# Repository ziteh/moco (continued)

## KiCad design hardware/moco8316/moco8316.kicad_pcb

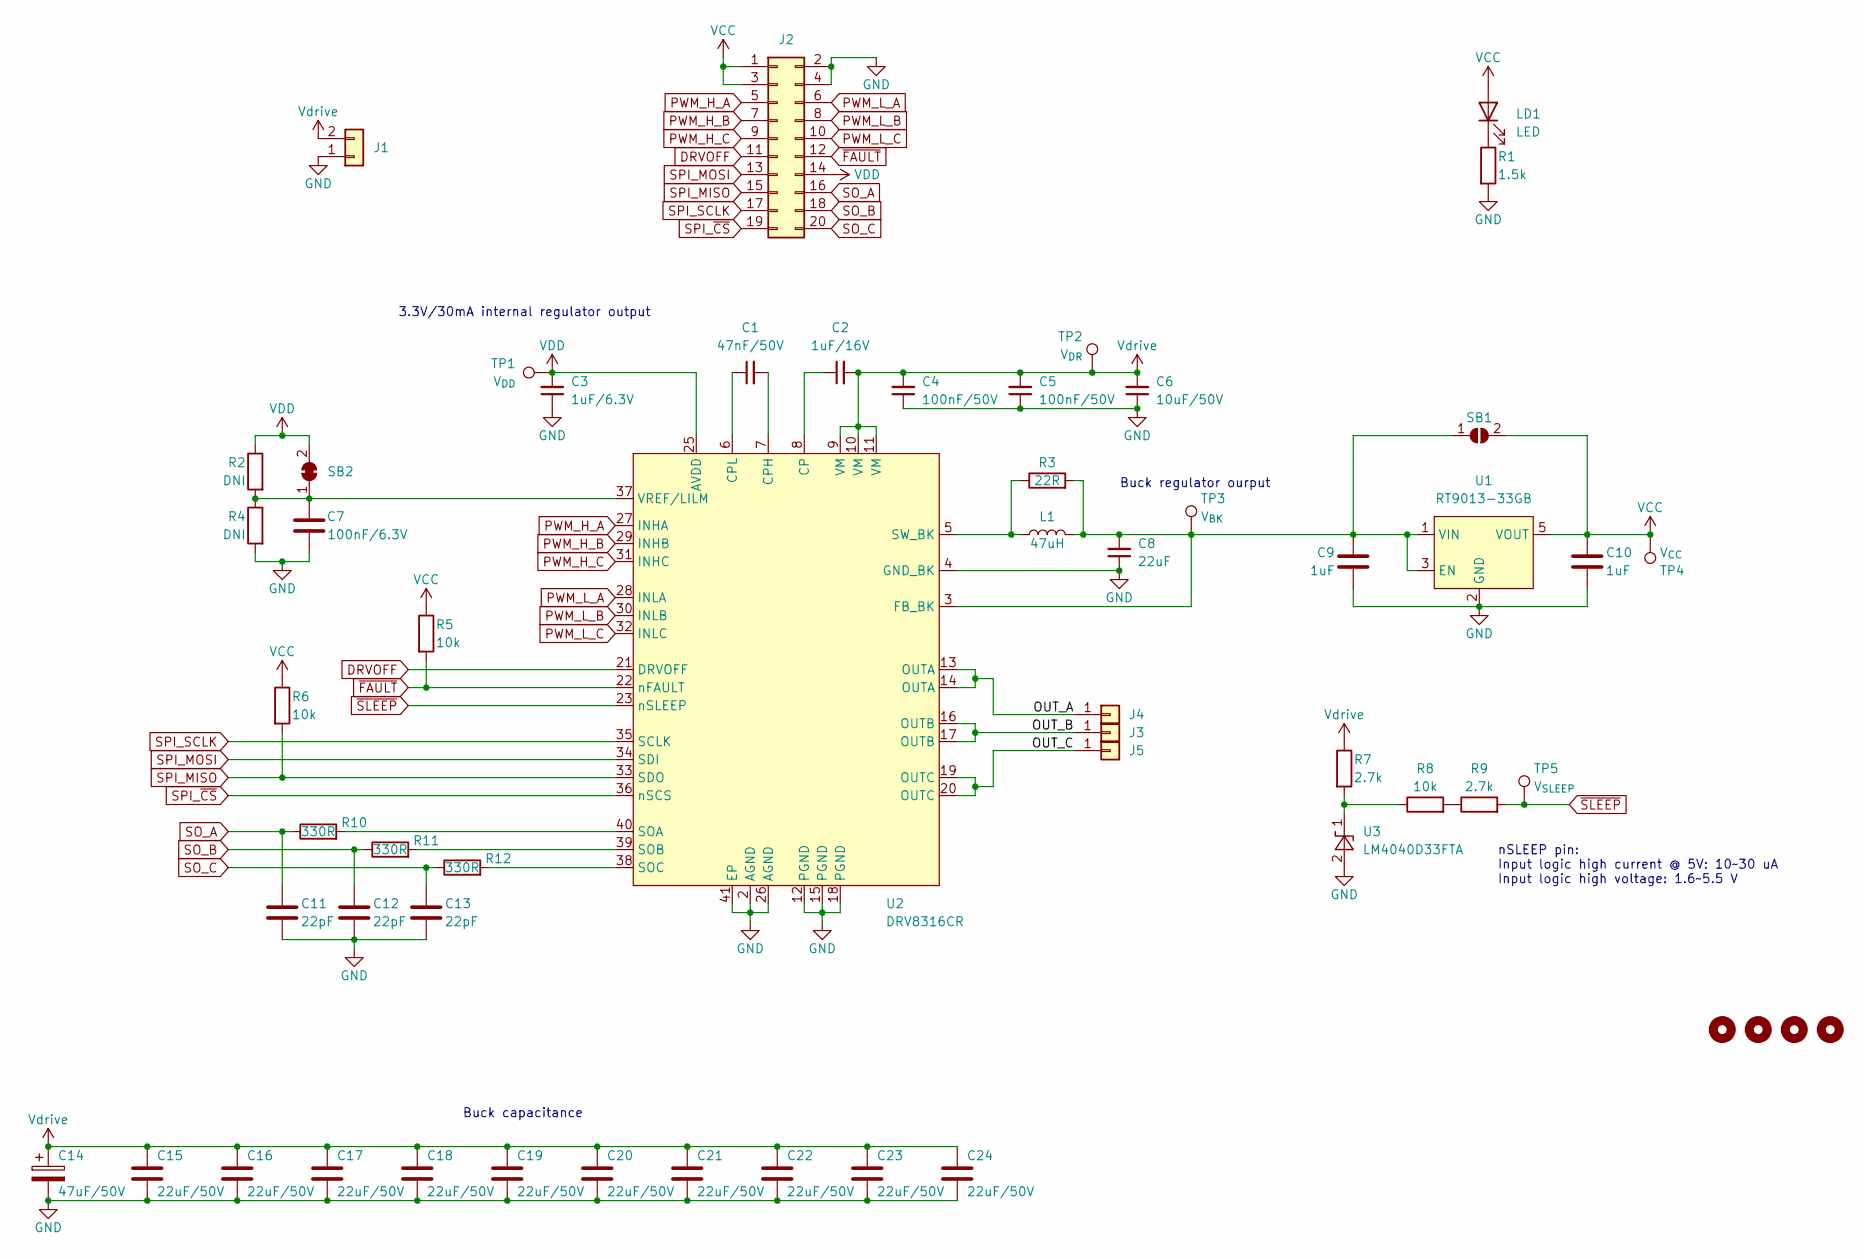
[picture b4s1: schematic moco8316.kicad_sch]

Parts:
C1: 47nF/50V; C_0603_1608Metric
C2: 1uF/16V; C_0603_1608Metric
C3: 1uF/6.3V; C_0603_1608Metric
C4, C5: 100nF/50V; C_0603_1608Metric
C6: 10uF/50V; C_0805_2012Metric; MFR. Part# GRM21BR61H106KE43L; LCSC C440198
C7: 100nF/6.3V; C_0603_1608Metric
C8: 22uF; C_0603_1608Metric
C9, C10: 1uF; C_0603_1608Metric
C11, C12, C13: 22pF; C_0603_1608Metric
C14: 47uF/50V; CP_Elec_6.3x7.7; MFR. Part# 50CE47AX; LCSC C179814
C15, C16, C17, C18, C19, C20, C21, C22, C23, C24: 22uF/50V; C_0805_2012Metric
H1, H2, H3, H4: MountingHole; MountingHole_3.2mm_M3
J1: Conn_01x02; AMASS_XT30UPB-M_1x02_P5.0mm_Vertical
J2: Conn_02x10_Odd_Even; PinSocket_2x10_P2.54mm_Vertical
J3, J4, J5: Conn_01x01; wire_3.2mm
L1: 47uH; L_Taiyo-Yuden_NR-50xx; MFR. Part# SM4532-470MT; LCSC C9899
LD1: LED; LED_0805_2012Metric_Pad1.15x1.40mm_HandSolder
R1: 1.5k; R_0603_1608Metric
R2, R4: DNI; R_0603_1608Metric
R3: 22R; R_0603_1608Metric
R5, R6, R8: 10k; R_0603_1608Metric
R7, R9: 2.7k; R_0603_1608Metric
R10, R11, R12: 330R; R_0603_1608Metric
SB1: SolderJumper_2_Open; SolderJumper-2_P1.3mm_Open_RoundedPad1.0x1.5mm
SB2: SolderJumper_2_Bridged; SolderJumper-2_P1.3mm_Bridged_RoundedPad1.0x1.5mm
TP1: V_{DD}; TestPoint_Pad_D1.0mm
TP2: V_{DR}; TestPoint_Pad_D1.0mm
TP3: V_{BK}; TestPoint_Pad_D1.0mm
TP4: V_{CC}; TestPoint_Pad_D1.0mm
TP5: V_{SLEEP}; TestPoint_Pad_D1.0mm
U1: RT9013-33GB; SOT-23-5
U2: DRV8316CR; VQFN-40_RGF_5x7mm_0.5mm_pitch_thermalpad
U3: LM4040D33FTA; SOT-23

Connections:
/OUT_A: J4.1, U2.13 (OUTA), U2.14 (OUTA)
/OUT_B: J3.1, U2.16 (OUTB), U2.17 (OUTB)
/OUT_C: J5.1, U2.19 (OUTC), U2.20 (OUTC)
DRVOFF: J2.11, U2.21 (DRVOFF)
GND: C3.1, C4.1, C5.1, C6.1, C7.2, C8.1, C9.2, C10.2, C11.2, C12.2, C13.2, C14.2, C15.2, C16.2, C17.2, C18.2, C19.2, C20.2, C21.2, C22.2, C23.2, C24.2, J1.1, J2.2, J2.4, R1.2, R4.2, U1.2 (GND), U2.2 (AGND), U2.4 (GND_BK), U2.12 (PGND), U2.15 (PGND), U2.18 (PGND), U2.26 (AGND), U2.41 (EP), U3.2 (A)
unnamed: LD1.1 (K), R1.1
unnamed: R8.2, R9.1
unnamed: C8.2, C9.1, L1.2, R3.2, SB1.1 (A), TP3.1, U1.1 (VIN), U1.3 (EN), U2.3 (FB_BK)
unnamed: C7.1, R2.2, R4.1, SB2.1 (A), U2.37 (VREF/LILM)
unnamed: C2.1, U2.8 (CP)
unnamed: C1.2, U2.7 (CPH)
unnamed: C1.1, U2.6 (CPL)
unnamed: R10.2, U2.40 (SOA)
unnamed: R11.2, U2.39 (SOB)
unnamed: R12.2, U2.38 (SOC)
unnamed: L1.1, R3.1, U2.5 (SW_BK)
unnamed: R7.2, R8.1, U3.1 (K)
PWM_H_A: J2.5, U2.27 (INHA)
PWM_H_B: J2.7, U2.29 (INHB)
PWM_H_C: J2.9, U2.31 (INHC)
PWM_L_A: J2.6, U2.28 (INLA)
PWM_L_B: J2.8, U2.30 (INLB)
PWM_L_C: J2.10, U2.32 (INLC)
SO_A: C11.1, J2.16, R10.1
SO_B: C12.1, J2.18, R11.1
SO_C: C13.1, J2.20, R12.1
SPI_MISO: J2.15, R6.2, U2.33 (SDO)
SPI_MOSI: J2.13, U2.34 (SDI)
SPI_SCLK: J2.17, U2.35 (SCLK)
SPI_~CS: J2.19, U2.36 (nSCS)
VCC: C10.1, J2.1, J2.3, LD1.2 (A), R5.1, R6.1, SB1.2 (B), TP4.1, U1.5 (VOUT)
VDD: C3.2, J2.14, R2.1, SB2.2 (B), TP1.1, U2.25 (AVDD)
Vdrive: C2.2, C4.2, C5.2, C6.2, C14.1, C15.1, C16.1, C17.1, C18.1, C19.1, C20.1, C21.1, C22.1, C23.1, C24.1, J1.2, R7.1, TP2.1, U2.9 (VM), U2.10 (VM), U2.11 (VM)
~FAULT: J2.12, R5.2, U2.22 (nFAULT)
~SLEEP: R9.2, TP5.1, U2.23 (nSLEEP)

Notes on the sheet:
3.3V/30mA internal regulator output
nSLEEP pin: Input logic high current @ 5V: 10~30 uA Input logic high voltage: 1.6~5.5 V
Buck regulator ourput
Buck capacitance

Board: 2 copper layers, 57 parts (0 on the bottom side), 35 nets, no tracks yet.

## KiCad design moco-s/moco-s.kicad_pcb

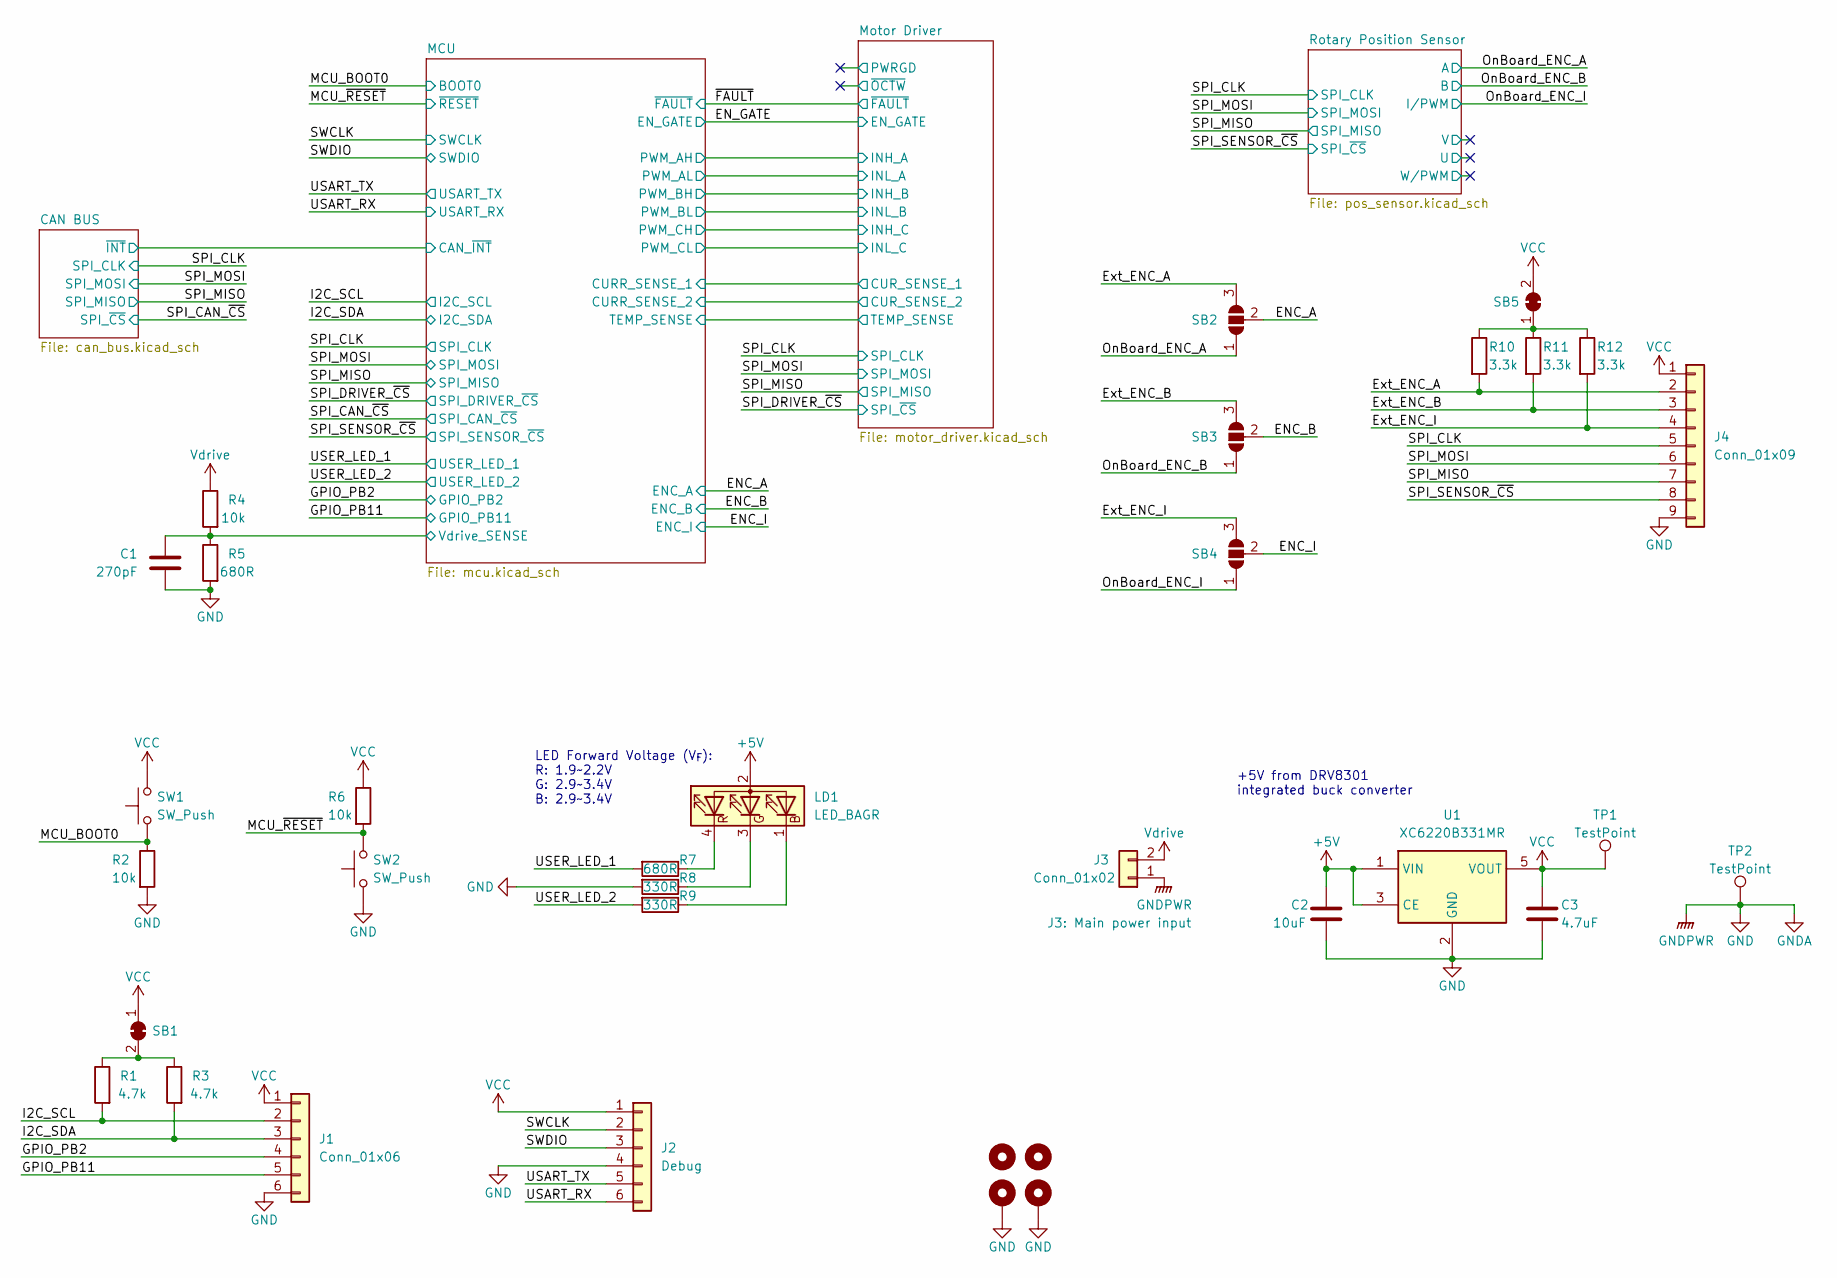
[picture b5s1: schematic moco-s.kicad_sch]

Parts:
C1: 270pF; C_0402_1005Metric; MFR.Part # GCM1555C1H271JA16D; JLCPCB Part # C524551
C2: 10uF; C_0402_1005Metric; MFR.Part # CL05A106MQ5NUNC; JLCPCB Part # C15525
C3: 4.7uF; C_0402_1005Metric; MFR.Part # CL05A475MP5NRNC; JLCPCB Part # C23733
H1, H3: MountingHole; MountingHole_2.2mm_M2_ISO14580
H2, H4: MountingHole_Pad; MountingHole_2.2mm_M2_Pad_Via
J1: Conn_01x06; JST_GH_SM06B-GHS-TB_1x06-1MP_P1.25mm_Horizontal; MFR.Part # GH1.25-6PWBPZ; JLCPCB Part # C2829255
J2: Debug; PinHeader_1x06_P2.54mm_Vertical
J3: Conn_01x02; AMASS_XT60-M_1x02_P7.20mm_Vertical; MFR.Part # XT60; JLCPCB Part # C98733
J4: Conn_01x09; JST_GH_SM09B-GHS-TB_1x09-1MP_P1.25mm_Horizontal; MFR.Part # GH1.25-9PWBPZ; JLCPCB Part # C2829258
LD1: LED_BAGR; RGB LED 1.6x1.6mm; MFR.Part # E6C0606RGBC3UDA; JLCPCB Part # C375569
R1, R3: 4.7k; R_0402_1005Metric; MFR.Part # 0402WGF4701TCE; JLCPCB Part # C25900
R2, R4, R6: 10k; R_0402_1005Metric; MFR.Part # 0402WGF1002TCE; JLCPCB Part # C25744
R5, R7: 680R; R_0402_1005Metric; MFR.Part # 0402WGF6800TCE; JLCPCB Part # C25130
R8, R9: 330R; R_0402_1005Metric; MFR.Part # 0402WGF3300TCE; JLCPCB Part # C25104
R10, R11, R12: 3.3k; R_0402_1005Metric; MFR.Part # 0402WGF3301TCE; JLCPCB Part # C25890
SB1, SB5: SolderJumper_2_Bridged; SolderJumper-2_P1.3mm_Bridged_RoundedPad1.0x1.5mm
SB2, SB3, SB4: Jumper_3_Bridged12; SolderJumper-3_P1.3mm_Open_RoundedPad1.0x1.5mm_NumberLabels
SW1, SW2: SW_Push; SW_SPST_CK_RS282G05A3; MFR.Part # TS-1092S-B3D2-G; JLCPCB Part # C520860
TP1, TP2: TestPoint; TestPoint_Pad_D2.0mm
U1: XC6220B331MR; SOT-23-5; MFR.Part # XC6220B331MR-G; JLCPCB Part # C86534

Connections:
+5V: C2.1, LD1.2 (A), U1.1 (VIN), U1.3 (CE); also elsewhere on the board
/ENC_A: SB2.2 (C); also elsewhere on the board
/ENC_B: SB3.2 (C); also elsewhere on the board
/ENC_I: SB4.2 (C); also elsewhere on the board
/Ext_ENC_A: J4.2, R10.2, SB2.3 (B)
/Ext_ENC_B: J4.3, R11.2, SB3.3 (B)
/Ext_ENC_I: J4.4, R12.2, SB4.3 (B)
/GPIO_PB2: J1.4; also elsewhere on the board
/GPIO_PB11: J1.5; also elsewhere on the board
/I2C_SCL: J1.2, R1.2; also elsewhere on the board
/I2C_SDA: J1.3, R3.2; also elsewhere on the board
/MCU/Vdrive_SENSE: C1.1, R4.2, R5.1; also elsewhere on the board
/MCU_BOOT0: R2.1, SW1.1; also elsewhere on the board
/MCU_~RESET: R6.2, SW2.2; also elsewhere on the board
/OnBoard_ENC_A: SB2.1 (A); also elsewhere on the board
/OnBoard_ENC_B: SB3.1 (A); also elsewhere on the board
/OnBoard_ENC_I: SB4.1 (A); also elsewhere on the board
/SPI_CLK: J4.5; also elsewhere on the board
/SPI_MISO: J4.7; also elsewhere on the board
/SPI_MOSI: J4.6; also elsewhere on the board
/SPI_SENSOR_~CS: J4.8; also elsewhere on the board
/SWCLK: J2.2; also elsewhere on the board
/SWDIO: J2.3; also elsewhere on the board
/USART_RX: J2.6; also elsewhere on the board
/USART_TX: J2.5; also elsewhere on the board
/USER_LED_1: R7.2; also elsewhere on the board
/USER_LED_2: R9.2; also elsewhere on the board
GND: C1.2, C2.2, C3.2, H2.1, H4.1, J1.6, J2.4, J3.1, J4.9, R2.2, R5.2, R8.2, SW2.1, TP2.1, U1.2 (GND); also elsewhere on the board
unnamed: LD1.1 (BK), R9.1
unnamed: LD1.3 (GK), R8.1
unnamed: LD1.4 (RK), R7.1
unnamed: R1.1, R3.1, SB1.2 (B)
unnamed: R10.1, R11.1, R12.1, SB5.1 (A)
VCC: C3.1, J1.1, J2.1, J4.1, R6.1, SB1.1 (A), SB5.2 (B), SW1.2, TP1.1, U1.5 (VOUT); also elsewhere on the board
Vdrive: J3.2, R4.1; also elsewhere on the board

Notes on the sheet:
LED Forward Voltage (V_{F}): R: 1.9~2.2V G: 2.9~3.4V B: 2.9~3.4V
+5V from DRV8301 integrated buck converter

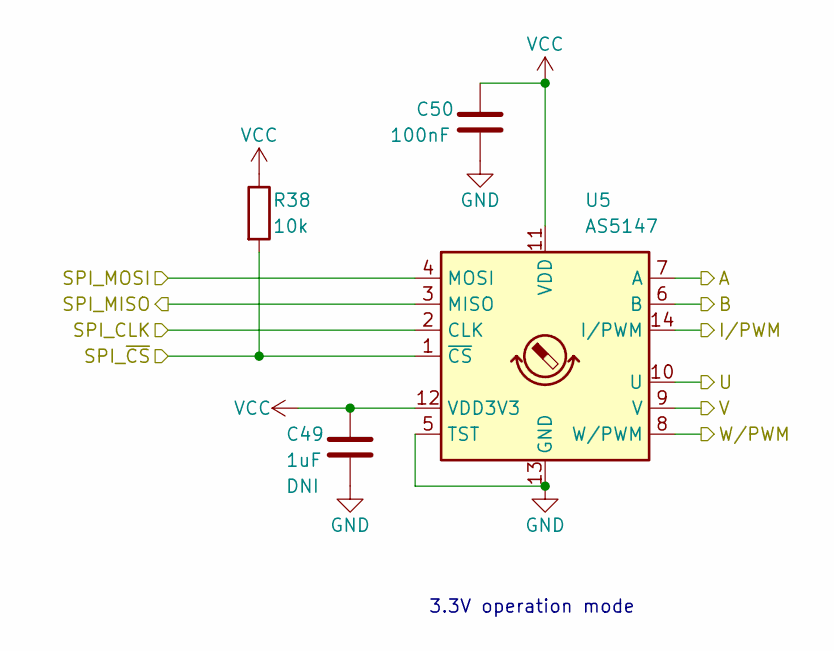
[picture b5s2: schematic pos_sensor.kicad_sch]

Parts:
C49: 1uF; C_0603_1608Metric
C50: 100nF; C_0603_1608Metric
R38: 10k; R_0402_1005Metric; MFR.Part # 0402WGF1002TCE; JLCPCB Part # C25744
U5: AS5147; TSSOP-14_4.4x5mm_P0.65mm; MFR.Part # AS5147P-HTSM; JLCPCB Part # C481876

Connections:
/OnBoard_ENC_A: U5.7 (A); also elsewhere on the board
/OnBoard_ENC_B: U5.6 (B); also elsewhere on the board
/OnBoard_ENC_I: U5.14 (I/PWM); also elsewhere on the board
/Rotary Position Sensor/U: U5.10 (U)
/Rotary Position Sensor/V: U5.9 (V)
/Rotary Position Sensor/W/PWM: U5.8 (W/PWM)
/SPI_CLK: U5.2 (CLK); also elsewhere on the board
/SPI_MISO: U5.3 (MISO); also elsewhere on the board
/SPI_MOSI: U5.4 (MOSI); also elsewhere on the board
/SPI_SENSOR_~CS: R38.2, U5.1 (~CS); also elsewhere on the board
GND: C49.2, C50.2, U5.5 (TST), U5.13 (GND); also elsewhere on the board
VCC: C49.1, C50.1, R38.1, U5.11 (VDD), U5.12 (VDD3V3); also elsewhere on the board

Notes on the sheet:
3.3V operation mode

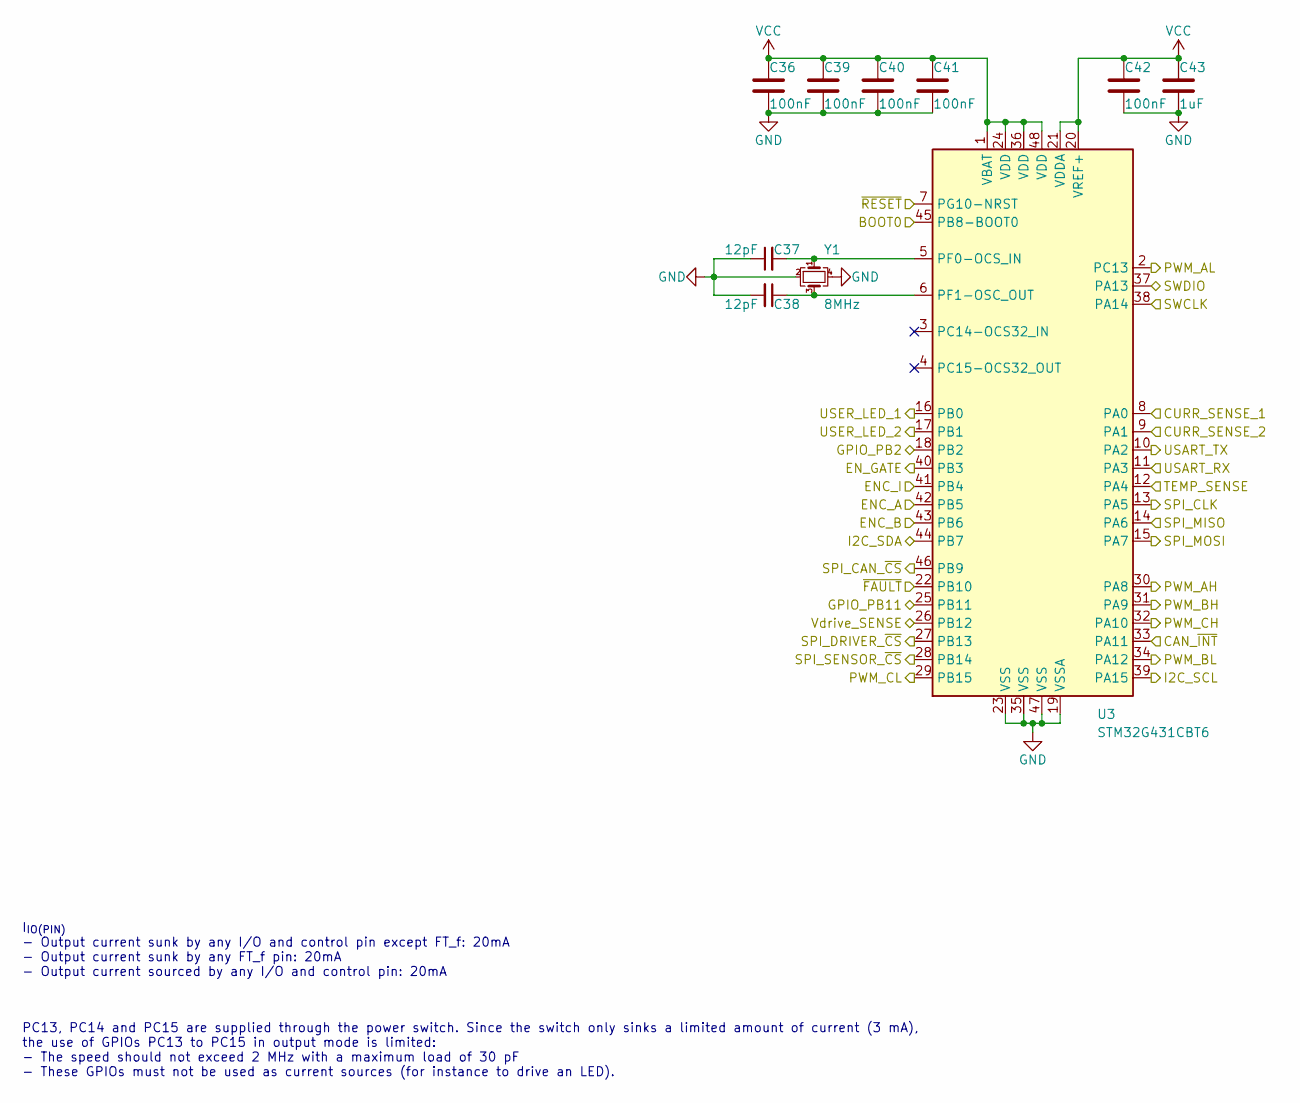
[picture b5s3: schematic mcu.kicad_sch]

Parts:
C36, C39, C40, C41, C42: 100nF; C_0402_1005Metric; MFR.Part # CL05B104KO5NNNC; JLCPCB Part # C1525
C37, C38: 12pF; C_0402_1005Metric; MFR.Part # 0402CG120J500NT; JLCPCB Part # C1547
C43: 1uF; C_0402_1005Metric; MFR.Part # CL05A105KA5NQNC; JLCPCB Part # C52923
U3: STM32G431CBT6; LQFP-48_7x7mm_P0.5mm; MFR.Part # STM32G431CBT6; JLCPCB Part # C529355
Y1: 8MHz; Crystal_SMD_3225-4Pin_3.2x2.5mm; MFR.Part # 1C208000BC0R; JLCPCB Part # C57131

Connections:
/CAN BUS/~INT: U3.33 (PA11); also elsewhere on the board
/ENC_A: U3.42 (PB5); also elsewhere on the board
/ENC_B: U3.43 (PB6); also elsewhere on the board
/ENC_I: U3.41 (PB4); also elsewhere on the board
/EN_GATE: U3.40 (PB3); also elsewhere on the board
/GPIO_PB2: U3.18 (PB2); also elsewhere on the board
/GPIO_PB11: U3.25 (PB11); also elsewhere on the board
/I2C_SCL: U3.39 (PA15); also elsewhere on the board
/I2C_SDA: U3.44 (PB7); also elsewhere on the board
/MCU/CURR_SENSE_1: U3.8 (PA0); also elsewhere on the board
/MCU/CURR_SENSE_2: U3.9 (PA1); also elsewhere on the board
/MCU/PWM_AH: U3.30 (PA8); also elsewhere on the board
/MCU/PWM_AL: U3.2 (PC13); also elsewhere on the board
/MCU/PWM_BH: U3.31 (PA9); also elsewhere on the board
/MCU/PWM_BL: U3.34 (PA12); also elsewhere on the board
/MCU/PWM_CH: U3.32 (PA10); also elsewhere on the board
/MCU/PWM_CL: U3.29 (PB15); also elsewhere on the board
/MCU/TEMP_SENSE: U3.12 (PA4); also elsewhere on the board
/MCU/Vdrive_SENSE: U3.26 (PB12); also elsewhere on the board
/MCU_BOOT0: U3.45 (PB8-BOOT0); also elsewhere on the board
/MCU_~RESET: U3.7 (PG10-NRST); also elsewhere on the board
/SPI_CAN_~CS: U3.46 (PB9); also elsewhere on the board
/SPI_CLK: U3.13 (PA5); also elsewhere on the board
/SPI_DRIVER_~CS: U3.27 (PB13); also elsewhere on the board
/SPI_MISO: U3.14 (PA6); also elsewhere on the board
/SPI_MOSI: U3.15 (PA7); also elsewhere on the board
/SPI_SENSOR_~CS: U3.28 (PB14); also elsewhere on the board
/SWCLK: U3.38 (PA14); also elsewhere on the board
/SWDIO: U3.37 (PA13); also elsewhere on the board
/USART_RX: U3.11 (PA3); also elsewhere on the board
/USART_TX: U3.10 (PA2); also elsewhere on the board
/USER_LED_1: U3.16 (PB0); also elsewhere on the board
/USER_LED_2: U3.17 (PB1); also elsewhere on the board
/~FAULT: U3.22 (PB10); also elsewhere on the board
GND: C36.2, C37.1, C38.2, C39.2, C40.2, C41.2, C42.2, C43.2, U3.19 (VSSA), U3.23 (VSS), U3.35 (VSS), U3.47 (VSS), Y1.2, Y1.4; also elsewhere on the board
unnamed: C37.2, U3.5 (PF0-OCS_IN), Y1.1
unnamed: C38.1, U3.6 (PF1-OSC_OUT), Y1.3
VCC: C36.1, C39.1, C40.1, C41.1, C42.1, C43.1, U3.1 (VBAT), U3.20 (VREF+), U3.21 (VDDA), U3.24 (VDD), U3.36 (VDD), U3.48 (VDD); also elsewhere on the board

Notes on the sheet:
I_{IO(PIN)} - Output current sunk by any I/O and control pin except FT_f: 20mA - Output current sunk by any FT_f pin: 20mA - Output current sourced by any I/O and control pin: 20mA
PC13, PC14 and PC15 are supplied through the power switch. Since the switch only sinks a limited amount of current (3 mA), the use of GPIOs PC13 to PC15 in output mode is limited: - The speed should not exceed 2 MHz with a maximum load of 30 pF - These GPIOs must not be used as current sources (for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

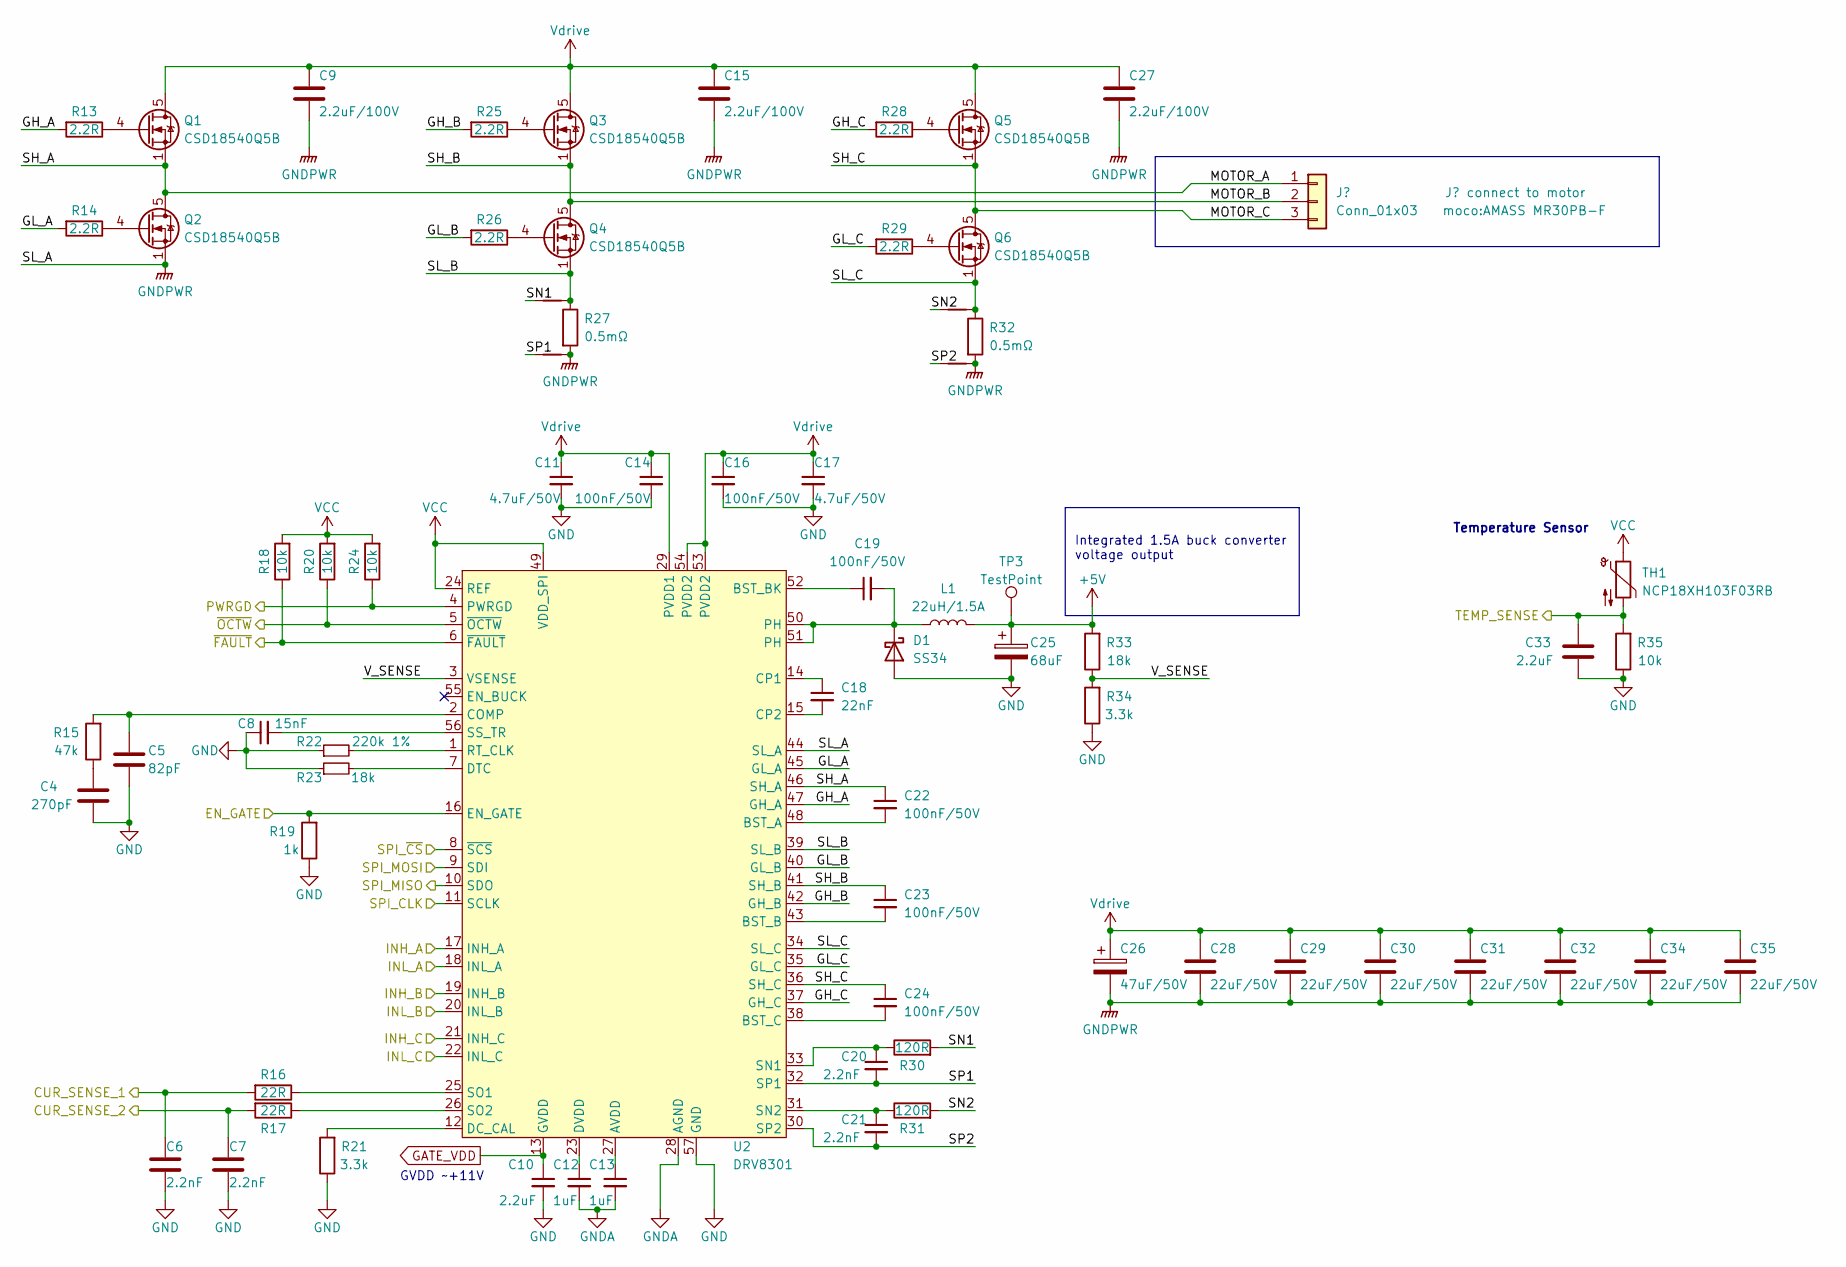
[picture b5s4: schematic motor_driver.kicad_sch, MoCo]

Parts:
C4: 270pF; C_0402_1005Metric; MFR.Part # GCM1555C1H271JA16D; JLCPCB Part # C524551
C5: 82pF; C_0402_1005Metric; MFR.Part # CC0402JRNPO9BN820; JLCPCB Part # C107011
C6, C7, C20, C21: 2.2nF; C_0603_1608Metric; MFR.Part # 0603B222K500NT; JLCPCB Part # C1604
C8: 15nF; C_0402_1005Metric; MFR.Part # CC0402KRX7R9BB153; JLCPCB Part # C114405
C9, C15, C27: 2.2uF/100V; C_1206_3216Metric; MFR.Part # HMK316AC7225KLHTE; JLCPCB Part # C650969
C10, C33: 2.2uF; C_0402_1005Metric; MFR.Part # 0402X225K160NT; JLCPCB Part # C501836
C11, C17: 4.7uF/50V; C_1206_3216Metric; MFR.Part # 1206B475K500NT; JLCPCB Part # C29823
C12, C13: 1uF; C_0402_1005Metric; MFR.Part # CL05A105KA5NQNC; JLCPCB Part # C52923
C14, C16, C19, C22, C23, C24: 100nF/50V; C_0603_1608Metric; MFR.Part # CC0603KRX7R9BB104; JLCPCB Part # C14663
C18: 22nF; C_0402_1005Metric; MFR.Part # 0402B223K500NT; JLCPCB Part # C1532
C25: 68uF; CP_EIA-6032-28_Kemet-C; MFR.Part # TAJC686K016RNJ; JLCPCB Part # C7220
C26: 47uF/50V; CP_Elec_6.3x7.7; MFR.Part # VES470M1HTR-0607; JLCPCB Part # C108053
C28, C29, C30, C31, C32, C34, C35: 22uF/50V; C_1210_3225Metric_Pad1.33x2.70mm_HandSolder
D1: SS34; D_SMA; MFR.Part # SS34; JLCPCB Part # C8678
L1: 22uH/1.5A; L_Bourns-SRN8040_8x8.15mm; MFR.Part # CKCS8040-22uH/M; JLCPCB Part # C354640
NT1, NT2, NT3, NT4: NetTie_2; NetTie-2_SMD_Pad0.5mm
Q1, Q2, Q3, Q4, Q5, Q6: CSD18540Q5B; TDSON-8-1; MFR.Part # CSD18540Q5B; JLCPCB Part # C86513
R13, R14, R25, R26, R28, R29: 2.2R; R_0603_1608Metric; MFR.Part # 0603WAJ022JT5E; JLCPCB Part # C25226
R15: 47k; R_0402_1005Metric; MFR.Part # 0402WGF4702TCE; JLCPCB Part # C25792
R16, R17: 22R; R_0402_1005Metric; MFR.Part # 0402WGF220JTCE; JLCPCB Part # C25092
R18, R20, R24, R35: 10k; R_0402_1005Metric; MFR.Part # 0402WGF1002TCE; JLCPCB Part # C25744
R19: 1k; R_0402_1005Metric; MFR.Part # 0402WGF1001TCE; JLCPCB Part # C11702
R21, R34: 3.3k; R_0402_1005Metric; MFR.Part # 0402WGF3301TCE; JLCPCB Part # C25890
R22: 220k 1%; R_0402_1005Metric; MFR.Part # 0402WGF2203TCE; JLCPCB Part # C25767
R23, R33: 18k; R_0402_1005Metric; MFR.Part # 0402WGF1802TCE; JLCPCB Part # C25762
R27, R32: 0.5mΩ; R_2512_6332Metric; MFR.Part # ASR-M-3-0.5F; JLCPCB Part # C469426
R30, R31: 120R; R_0402_1005Metric; MFR.Part # 0402WGF1200TCE; JLCPCB Part # C25079
TH1: NCP18XH103F03RB; R_0603_1608Metric; MFR.Part # NCP18XH103F03RB; JLCPCB Part # C13564
TP3: TestPoint; TestPoint_Pad_D2.0mm
U2: DRV8301; HTSSOP-56-1EP_6.1x14mm_P0.5mm_EP3.61x6.35mm; MFR.Part # DRV8301DCAR; JLCPCB Part # C98969

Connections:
+5V: C25.1, L1.2, R33.2, TP3.1; also elsewhere on the board
/EN_GATE: R19.2, U2.16 (EN_GATE); also elsewhere on the board
/MCU/CURR_SENSE_1: C6.1, R16.2; also elsewhere on the board
/MCU/CURR_SENSE_2: C7.1, R17.2; also elsewhere on the board
/MCU/PWM_AH: U2.17 (INH_A); also elsewhere on the board
/MCU/PWM_AL: U2.18 (INL_A); also elsewhere on the board
/MCU/PWM_BH: U2.19 (INH_B); also elsewhere on the board
/MCU/PWM_BL: U2.20 (INL_B); also elsewhere on the board
/MCU/PWM_CH: U2.21 (INH_C); also elsewhere on the board
/MCU/PWM_CL: U2.22 (INL_C); also elsewhere on the board
/MCU/TEMP_SENSE: C33.1, R35.2, TH1.2; also elsewhere on the board
/Motor Driver/GH_A: R13.2, U2.47 (GH_A)
/Motor Driver/GH_B: R25.2, U2.42 (GH_B)
/Motor Driver/GH_C: R28.2, U2.37 (GH_C)
/Motor Driver/GL_A: R14.2, U2.45 (GL_A)
/Motor Driver/GL_B: R26.2, U2.40 (GL_B)
/Motor Driver/GL_C: R29.2, U2.35 (GL_C)
/Motor Driver/MOTOR_A: C22.1, Q1.1 (S), Q1.2 (S), Q1.3 (S), Q2.5 (D), U2.46 (SH_A); also elsewhere on the board
/Motor Driver/MOTOR_B: C23.1, Q3.1 (S), Q3.2 (S), Q3.3 (S), Q4.5 (D), U2.41 (SH_B); also elsewhere on the board
/Motor Driver/MOTOR_C: C24.1, Q5.1 (S), Q5.2 (S), Q5.3 (S), Q6.5 (D), U2.36 (SH_C); also elsewhere on the board
/Motor Driver/PWRGD: R24.1, U2.4 (PWRGD)
/Motor Driver/SL_B: NT1.2, Q4.1 (S), Q4.2 (S), Q4.3 (S), R27.1, U2.39 (SL_B)
/Motor Driver/SL_C: NT3.2, Q6.1 (S), Q6.2 (S), Q6.3 (S), R32.1, U2.34 (SL_C)
/Motor Driver/SN1: NT1.1, R30.2
/Motor Driver/SN2: NT3.1, R31.2
/Motor Driver/SP1: C20.2, NT2.1, U2.32 (SP1)
/Motor Driver/SP2: C21.2, NT4.1, U2.30 (SP2)
/Motor Driver/V_SENSE: R33.1, R34.2, U2.3 (VSENSE)
/Motor Driver/~OCTW: R20.1, U2.5 (~OCTW)
/SPI_CLK: U2.11 (SCLK); also elsewhere on the board
/SPI_DRIVER_~CS: U2.8 (~SCS); also elsewhere on the board
/SPI_MISO: U2.10 (SDO); also elsewhere on the board
/SPI_MOSI: U2.9 (SDI); also elsewhere on the board
/~FAULT: R18.1, U2.6 (~FAULT); also elsewhere on the board
GATE_VDD: C10.1, U2.13 (GVDD)
GND: C4.2, C5.2, C6.2, C7.2, C8.1, C9.2, C10.2, C11.2, C12.2, C13.2, C14.2, C15.2, C16.2, C17.2, C25.2, C26.2, C27.2, C28.2, C29.2, C30.2, C31.2, C32.2, C33.2, C34.2, C35.2, D1.2 (A), NT2.2, NT4.2, Q2.1 (S), Q2.2 (S), Q2.3 (S), R19.1, R21.1, R22.1, R23.1, R27.2, R32.2, R34.1, R35.1, U2.28 (AGND), U2.44 (SL_A), U2.57 (GND); also elsewhere on the board
unnamed: C4.1, R15.1
unnamed: C5.1, R15.2, U2.2 (COMP)
unnamed: C8.2, U2.56 (SS_TR)
unnamed: C12.1, U2.23 (DVDD)
unnamed: C13.1, U2.27 (AVDD)
unnamed: C18.1, U2.14 (CP1)
unnamed: C18.2, U2.15 (CP2)
unnamed: C19.1, U2.52 (BST_BK)
unnamed: C19.2, D1.1 (K), L1.1, U2.50 (PH), U2.51 (PH)
unnamed: C20.1, R30.1, U2.33 (SN1)
unnamed: C21.1, R31.1, U2.31 (SN2)
unnamed: C22.2, U2.48 (BST_A)
unnamed: C23.2, U2.43 (BST_B)
unnamed: C24.2, U2.38 (BST_C)
unnamed: Q1.4 (G), R13.1
unnamed: Q2.4 (G), R14.1
unnamed: Q3.4 (G), R25.1
unnamed: Q4.4 (G), R26.1
unnamed: Q5.4 (G), R28.1
unnamed: Q6.4 (G), R29.1
unnamed: R16.1, U2.25 (SO1)
unnamed: R17.1, U2.26 (SO2)
unnamed: R21.2, U2.12 (DC_CAL)
unnamed: R22.2, U2.1 (RT_CLK)
unnamed: R23.2, U2.7 (DTC)
VCC: R18.2, R20.2, R24.2, TH1.1, U2.24 (REF), U2.49 (VDD_SPI); also elsewhere on the board
Vdrive: C9.1, C11.1, C14.1, C15.1, C16.1, C17.1, C26.1, C27.1, C28.1, C29.1, C30.1, C31.1, C32.1, C34.1, C35.1, Q1.5 (D), Q3.5 (D), Q5.5 (D), U2.29 (PVDD1), U2.53 (PVDD2), U2.54 (PVDD2); also elsewhere on the board

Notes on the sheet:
Integrated 1.5A buck converter voltage output
Temperature Sensor
GVDD ~+11V

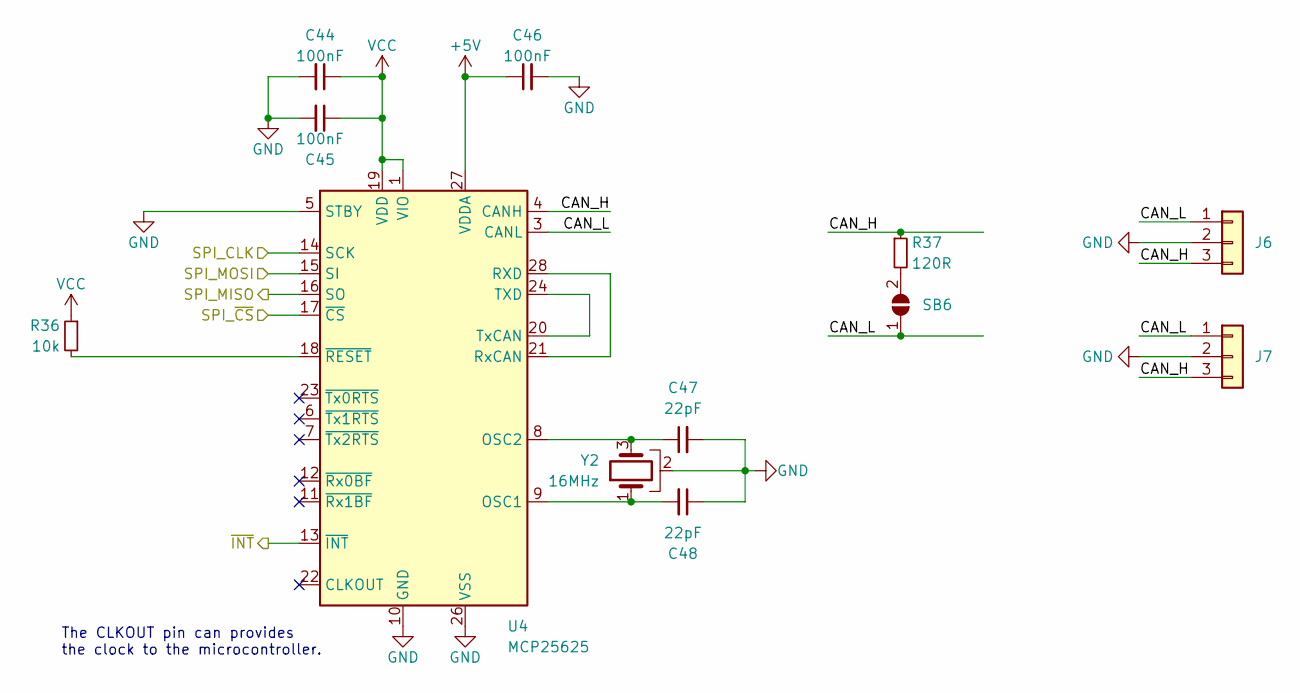
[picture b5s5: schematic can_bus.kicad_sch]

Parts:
C44, C45, C46: 100nF; C_0402_1005Metric; MFR.Part # CL05B104KO5NNNC; JLCPCB Part # C1525
C47, C48: 22pF; C_0402_1005Metric; MFR.Part # CL10C220JB8NNNC; JLCPCB Part # C1653
J6, J7: Conn_02x02_Top_Bottom; JST_GH_SM03B-GHS-TB_1x03-1MP_P1.25mm_Horizontal; MFR.Part # GH1.25-3PWBPZ; JLCPCB Part # C2829252
R36: 10k; R_0402_1005Metric; MFR.Part # 0402WGF1002TCE; JLCPCB Part # C25744
R37: 120R; R_0402_1005Metric; MFR.Part # 0402WGF1200TCE; JLCPCB Part # C25079
SB6: SolderJumper_2_Open; SolderJumper-2_P1.3mm_Open_TrianglePad1.0x1.5mm
U4: MCP25625; QFN-28-1EP_6x6mm_P0.65mm_EP4.25x4.25mm; MFR.Part # MCP25625T-E/ML; JLCPCB Part # C191253
Y2: 16MHz; Crystal_SMD_3225-4Pin_3.2x2.5mm; MFR.Part # X322516MLB4SI; JLCPCB Part # C13738

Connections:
+5V: C46.1, U4.27 (VDDA); also elsewhere on the board
/CAN BUS/CAN_H: J6.3, J7.3, R37.1, U4.4 (CANH)
/CAN BUS/CAN_L: J6.1, J7.1, SB6.1 (A), U4.3 (CANL)
/CAN BUS/~INT: U4.13 (~INT); also elsewhere on the board
/SPI_CAN_~CS: U4.17 (~CS); also elsewhere on the board
/SPI_CLK: U4.14 (SCK); also elsewhere on the board
/SPI_MISO: U4.16 (SO); also elsewhere on the board
/SPI_MOSI: U4.15 (SI); also elsewhere on the board
GND: C44.2, C45.2, C46.2, C47.2, C48.1, J6.2, J7.2, U4.5 (STBY), U4.10 (GND), U4.26 (VSS), Y2.2; also elsewhere on the board
unnamed: C47.1, U4.8 (OSC2), Y2.3
unnamed: C48.2, U4.9 (OSC1), Y2.1
unnamed: R36.2, U4.18 (~RESET)
unnamed: R37.2, SB6.2 (B)
unnamed: U4.20 (TxCAN), U4.24 (TXD)
unnamed: U4.21 (RxCAN), U4.28 (RXD)
VCC: C44.1, C45.1, R36.1, U4.1 (VIO), U4.19 (VDD); also elsewhere on the board

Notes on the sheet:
The CLKOUT pin can provides the clock to the microcontroller.
